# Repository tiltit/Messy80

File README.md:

Messy80 
Z80 single board computer

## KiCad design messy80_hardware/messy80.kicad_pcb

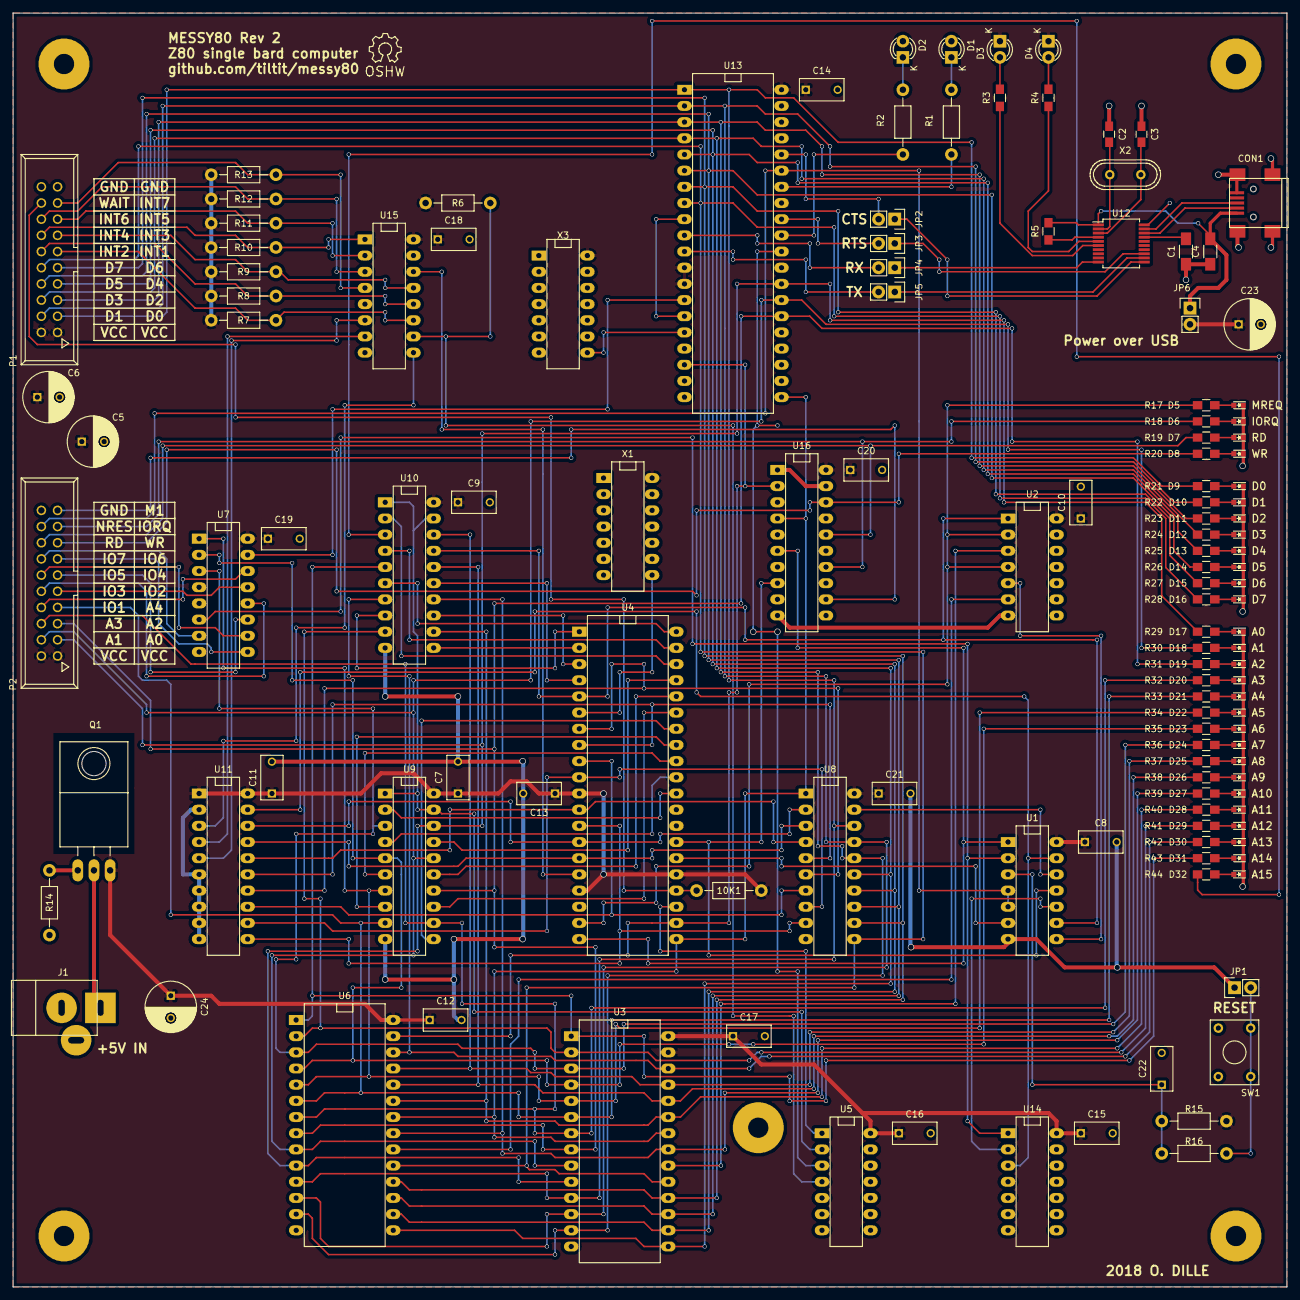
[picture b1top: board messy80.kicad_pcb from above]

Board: 2 copper layers, 200.0 x 200.0 mm, 132 parts (0 on the bottom side), 150 nets.

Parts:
10K1: R; Resistor_Horizontal_RM10mm
C1: 0.47uf; C_1206_HandSoldering
C2, C3: 18pf; C_0805_HandSoldering
C4: 1uf; C_1206_HandSoldering
C5, C6, C23, C24: 330uf; C_Radial_D8_L11.5_P3.5
C7, C8, C9, C10, C11, C12, C13, C14, C15, C16, C17, C18, C19, C20, C21, C22: 100nf; C_Rect_L7_W3.5_P5
CON1: USB-MINI-B; USB_Mini-B
D1, D2, D3, D4: LED; LED-3MM
D5, D6, D7, D8, D9, D10, D11, D12, D13, D14, D15, D16, D17, D18, D19, D20, D21, D22, D23, D24, D25, D26, D27, D28, D29, D30, D31, D32: LED; LED-0603
J1: Conn_01x02; JACK_ALIM
JP1, JP6: Jumper_NO_Small; Pin_Header_Straight_1x02
JP2, JP3, JP4, JP5: Jumper_NC_Small; Pin_Header_Straight_1x02
P1, P2: CONN_02X10; VASCH10x2
Q1: IRF9540N; TO-220_Neutral123_Horizontal_LargePads
R1, R2, R16: 1K; Resistor_Horizontal_RM10mm
R3, R4: 1K; R_0805_HandSoldering
R5: 10K; R_0805_HandSoldering
R6, R7, R8, R10, R11, R12, R13, R15: 10K; Resistor_Horizontal_RM10mm
R9: R; Resistor_Horizontal_RM10mm
R14: 100K; Resistor_Horizontal_RM10mm
R17, R18, R19, R20, R21, R22, R23, R24, R25, R26, R27, R28, R29, R30, R31, R32, R33, R34, R35, R36, R37, R38, R39, R40, R41, R42, R43, R44: R; R_0805_HandSoldering
SW1: SW_PUSH; Puch_button_TH
U1: 74LS14; DIP-14__300_ELL
U2: 74LS32; DIP-14__300_ELL
U3: 28C256; DIP-28__600_ELL
U4: Z80-CPU; DIP-40__600_ELL
U5: 74LS04; DIP-14__300_ELL
U6: KM62256ALP-8; DIP-28__600_ELL
U7: 74LS138; DIP-16__300_ELL
U8, U11: 74LS245; DIP-20__300_ELL
U9, U10, U16: 74LS244; DIP-20__300_ELL
U12: MPC2200; SSOP-20_5.3x7.2mm_Pitch0.65mm
U13: 16550; DIP-40__600_ELL
U14: 74LS00; DIP-14__300_ELL
U15: 74LS148; DIP-16__300_ELL
X1: 4Mhz; DIP-14__300_ELL
X2: 12MHz; Crystal_HC49-U_Vertical
X3: 1.8432MHz; DIP-14__300_ELL

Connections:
/D+: CON1.3, U12.19
/D-: CON1.2, U12.18
A0: U4.30, U9.2
A1: U4.31, U9.4
A2: U4.32, U9.6
A3: U4.33, U9.8
A4: U4.34, U9.11
A5: U4.35, U9.13
A6: U4.36, U9.15
A7: U4.37, U9.17
A8: U4.38, U10.2
A9: U4.39, U10.4
A10: U4.40, U10.6
A11: U4.1, U10.8
A12: U4.2, U10.11
A13: U4.3, U10.13
A14: U4.4, U10.15
A15: U1.9, U2.1, U4.5, U10.17
AB0: P2.3, R29.2, U3.10, U6.10, U9.18, U13.28
AB1: P2.4, R30.2, U3.9, U6.9, U9.16, U13.27
AB2: P2.5, R31.2, U3.8, U6.8, U9.14, U13.26
AB3: P2.6, R32.2, U3.7, U6.7, U9.12
AB4: P2.7, R33.2, U3.6, U6.6, U9.9
AB5: R34.2, U3.5, U6.5, U7.1, U9.7
AB6: R35.2, U3.4, U6.4, U7.2, U9.5
AB7: R36.2, U3.3, U6.3, U7.3, U9.3
AB8: R37.2, U3.25, U6.25, U10.18
AB9: R38.2, U3.24, U6.24, U10.16
AB10: R39.2, U3.21, U6.21, U10.14
AB11: R40.2, U3.23, U6.23, U10.12
AB12: R41.2, U3.2, U6.2, U10.9
AB13: R42.2, U3.26, U6.26, U10.7
AB14: R43.2, U3.1, U6.1, U10.5
AB15: R44.2, U10.3
BUSAK: U4.23, U5.1
D0: U4.14, U8.2, U11.18
D1: U4.15, U8.3, U11.17
D2: U4.12, U8.4, U11.16
D3: U4.8, U8.5, U11.15
D4: U4.7, U8.6, U11.14
D5: U4.9, U8.7, U11.13
D6: U4.10, U8.8, U11.12
D7: U4.13, U8.9, U11.11
DATA_ENABLE: U1.12, U8.19
DB0: P1.3, R21.2, U3.11, U6.11, U8.18, U13.1
DB1: P1.4, R22.2, U3.12, U6.12, U8.17, U13.2
DB2: P1.5, R23.2, U3.13, U6.13, U8.16, U13.3
DB3: P1.6, R24.2, U3.15, U6.15, U8.15, U13.4
DB4: P1.7, R25.2, U3.16, U6.16, U8.14, U13.5
DB5: P1.8, R26.2, U3.17, U6.17, U8.13, U13.6
DB6: P1.9, R27.2, U3.18, U6.18, U8.12, U13.7
DB7: P1.10, R28.2, U3.19, U6.19, U8.11, U13.8
GND: C1.1, C2.1, C3.1, C4.1, C5.2, C6.2, C7.2, C8.2, C9.2, C10.2, C11.2, C12.2, C13.2, C14.2, C15.2, C16.2, C17.2, C18.2, C19.2, C20.2, C21.2, C22.2, C23.2, C24.2, CON1.5, CON1.6, D1.2, D2.2, D5.1, D6.1, D7.1, D8.1, D9.1, D10.1, D11.1, D12.1, D13.1, D14.1, D15.1, D16.1, D17.1, D18.1, D19.1, D20.1, D21.1, D22.1, D23.1, D24.1, D25.1, D26.1, D27.1, D28.1, D29.1, D30.1, D31.1, D32.1, J1.2, JP1.1, P1.19, P1.20, P2.20, R14.2, SW1.1, U1.7, U2.7, U3.14, U4.29, U5.7, U6.14, U7.4, U7.5, U7.8, U8.10, U9.10, U10.10, U11.2, U11.6, U11.7, U11.8, U11.9, U11.10, U12.20, U13.19, U13.20, U13.22, U13.25, U14.7, U15.5, U15.8, U16.1, U16.10, U16.19, X1.7, X3.7
INT: U4.16, U15.14
INT0: R6.2, U5.4, U15.10
INT1: P1.11, R7.2, U15.11
INT2: P1.12, R8.2, U15.12
INT3: P1.13, R9.2, U15.13
INT4: P1.14, R10.2, U15.1
INT5: P1.15, R11.2, U15.2
INT6: P1.16, R12.2, U15.3
INT7: P1.17, R13.2, U15.4
INT_RD_ENABLE: U1.13, U11.19, U14.3
IO0: U7.15, U13.14
IO1: P2.8, U7.14
IO2: P2.9, U7.13
IO3: P2.10, U7.12
IO4: P2.11, U7.11
IO5: P2.12, U7.10
IO6: P2.13, U7.9
IO7: P2.14, U7.7
IORQ: U1.1, U4.20, U16.6
IORQ_B: P2.17, R18.2, U16.14
M1: U1.11, U4.27, U16.8
M1_B: P2.19, U16.12
MREQ: R17.2, U2.2, U2.4, U4.19
NIORQ: U1.2, U7.6, U14.1
NRESET: P2.18, U1.4, U1.5, U13.35
unnamed: C1.2, U12.17
unnamed: C2.2, U12.2, X2.1
unnamed: C3.2, U12.3, X2.2
unnamed: C4.2, CON1.1, JP6.1, R5.2, U12.1
unnamed: C22.1, R15.2, R16.1, U1.3
unnamed: D1.1, R1.2
unnamed: D2.1, R2.2
unnamed: D3.2, R3.2
unnamed: D4.2, R4.2
unnamed: D5.2, R17.1
unnamed: D6.2, R18.1
unnamed: D7.2, R19.1
unnamed: D8.2, R20.1
unnamed: D9.2, R21.1
unnamed: D10.2, R22.1
unnamed: D11.2, R23.1
unnamed: D12.2, R24.1
unnamed: D13.2, R25.1
unnamed: D14.2, R26.1
unnamed: D15.2, R27.1
unnamed: D16.2, R28.1
unnamed: D17.2, R29.1
unnamed: D18.2, R30.1
unnamed: D19.2, R31.1
unnamed: D20.2, R32.1
unnamed: D21.2, R33.1
unnamed: D22.2, R34.1
unnamed: D23.2, R35.1
unnamed: D24.2, R36.1
unnamed: D25.2, R37.1
unnamed: D26.2, R38.1
unnamed: D27.2, R39.1
unnamed: D28.2, R40.1
unnamed: D29.2, R41.1
unnamed: D30.2, R42.1
unnamed: D31.2, R43.1
unnamed: D32.2, R44.1
unnamed: J1.1, Q1.2
unnamed: JP1.2, R16.2, SW1.2
unnamed: JP2.1, U12.11
unnamed: JP2.2, U13.36
unnamed: JP3.1, U12.13
unnamed: JP3.2, U13.32
unnamed: JP4.1, U12.10
unnamed: JP4.2, U13.10
unnamed: JP5.1, U12.12
unnamed: JP5.2, U13.11
unnamed: Q1.1, R14.1
unnamed: R1.1, U13.34
unnamed: R2.1, U13.31
unnamed: R3.1, U12.6
unnamed: R4.1, U12.5
unnamed: R5.1, U12.4
unnamed: U1.8, U2.5
unnamed: U1.10, U14.2
unnamed: U2.3, U3.20
unnamed: U2.6, U6.20
unnamed: U4.6, X1.8
unnamed: U5.2, U9.1, U9.19, U10.1, U10.19
unnamed: U11.3, U15.9
unnamed: U11.4, U15.7
unnamed: U11.5, U15.6
unnamed: U13.9, U13.15
unnamed: U13.16, X3.8
unnamed: U5.3, U13.30
RD: U3.22, U4.21, U6.22, U8.1, U13.21, U16.4
RD_B: P2.16, R19.2, U16.16
RESET: U1.6, U4.26
VCC: 10K1.2, C5.1, C6.1, C7.1, C8.1, C9.1, C10.1, C11.1, C12.1, C13.1, C14.1, C15.1, C16.1, C17.1, C18.1, C19.1, C20.1, C21.1, C23.1, C24.1, D3.1, D4.1, JP6.2, P1.1, P1.2, P2.1, P2.2, Q1.3, R6.1, R7.1, R8.1, R9.1, R10.1, R11.1, R12.1, R13.1, R15.1, U1.14, U2.14, U3.27, U3.28, U4.11, U4.17, U4.25, U5.14, U6.28, U7.16, U8.20, U9.20, U10.20, U11.1, U11.20, U13.12, U13.13, U13.40, U14.14, U15.16, U16.20, X1.14, X3.14
WAIT: 10K1.1, P1.18, U4.24
WR: U4.22, U6.27, U13.18, U16.2
WR_B: P2.15, R20.2, U16.18

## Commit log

2018-03-11 small fix
2018-03-19 adding makefiles
2018-03-20 Added adump command to messymonitor
2018-03-21 Firt C program for the Messy80
